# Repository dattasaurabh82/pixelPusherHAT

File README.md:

## PixelPusherHAT
Based on [hzeller's HW hat design](https://github.com/hzeller/rpi-rgb-led-matrix/tree/dfc27c15c224a92496034a39512a274744879e86/adapter/active-3) in the footprint of a HAT, designed in Eagle with minor modifications.

### [The schematic](/assetsREF/PixelPusherV0.pdf)

The managed library for Eagle and Fusion 360 can be found [here](https://library.io/libraries/29033116-PixelPusherV0): 

### _Note_: The GERBERs were generated using [jlcpcb's cam script](https://support.jlcpcb.com/article/137-how-to-generate-gerber-and-drill-files-in-autodesk-eagle).

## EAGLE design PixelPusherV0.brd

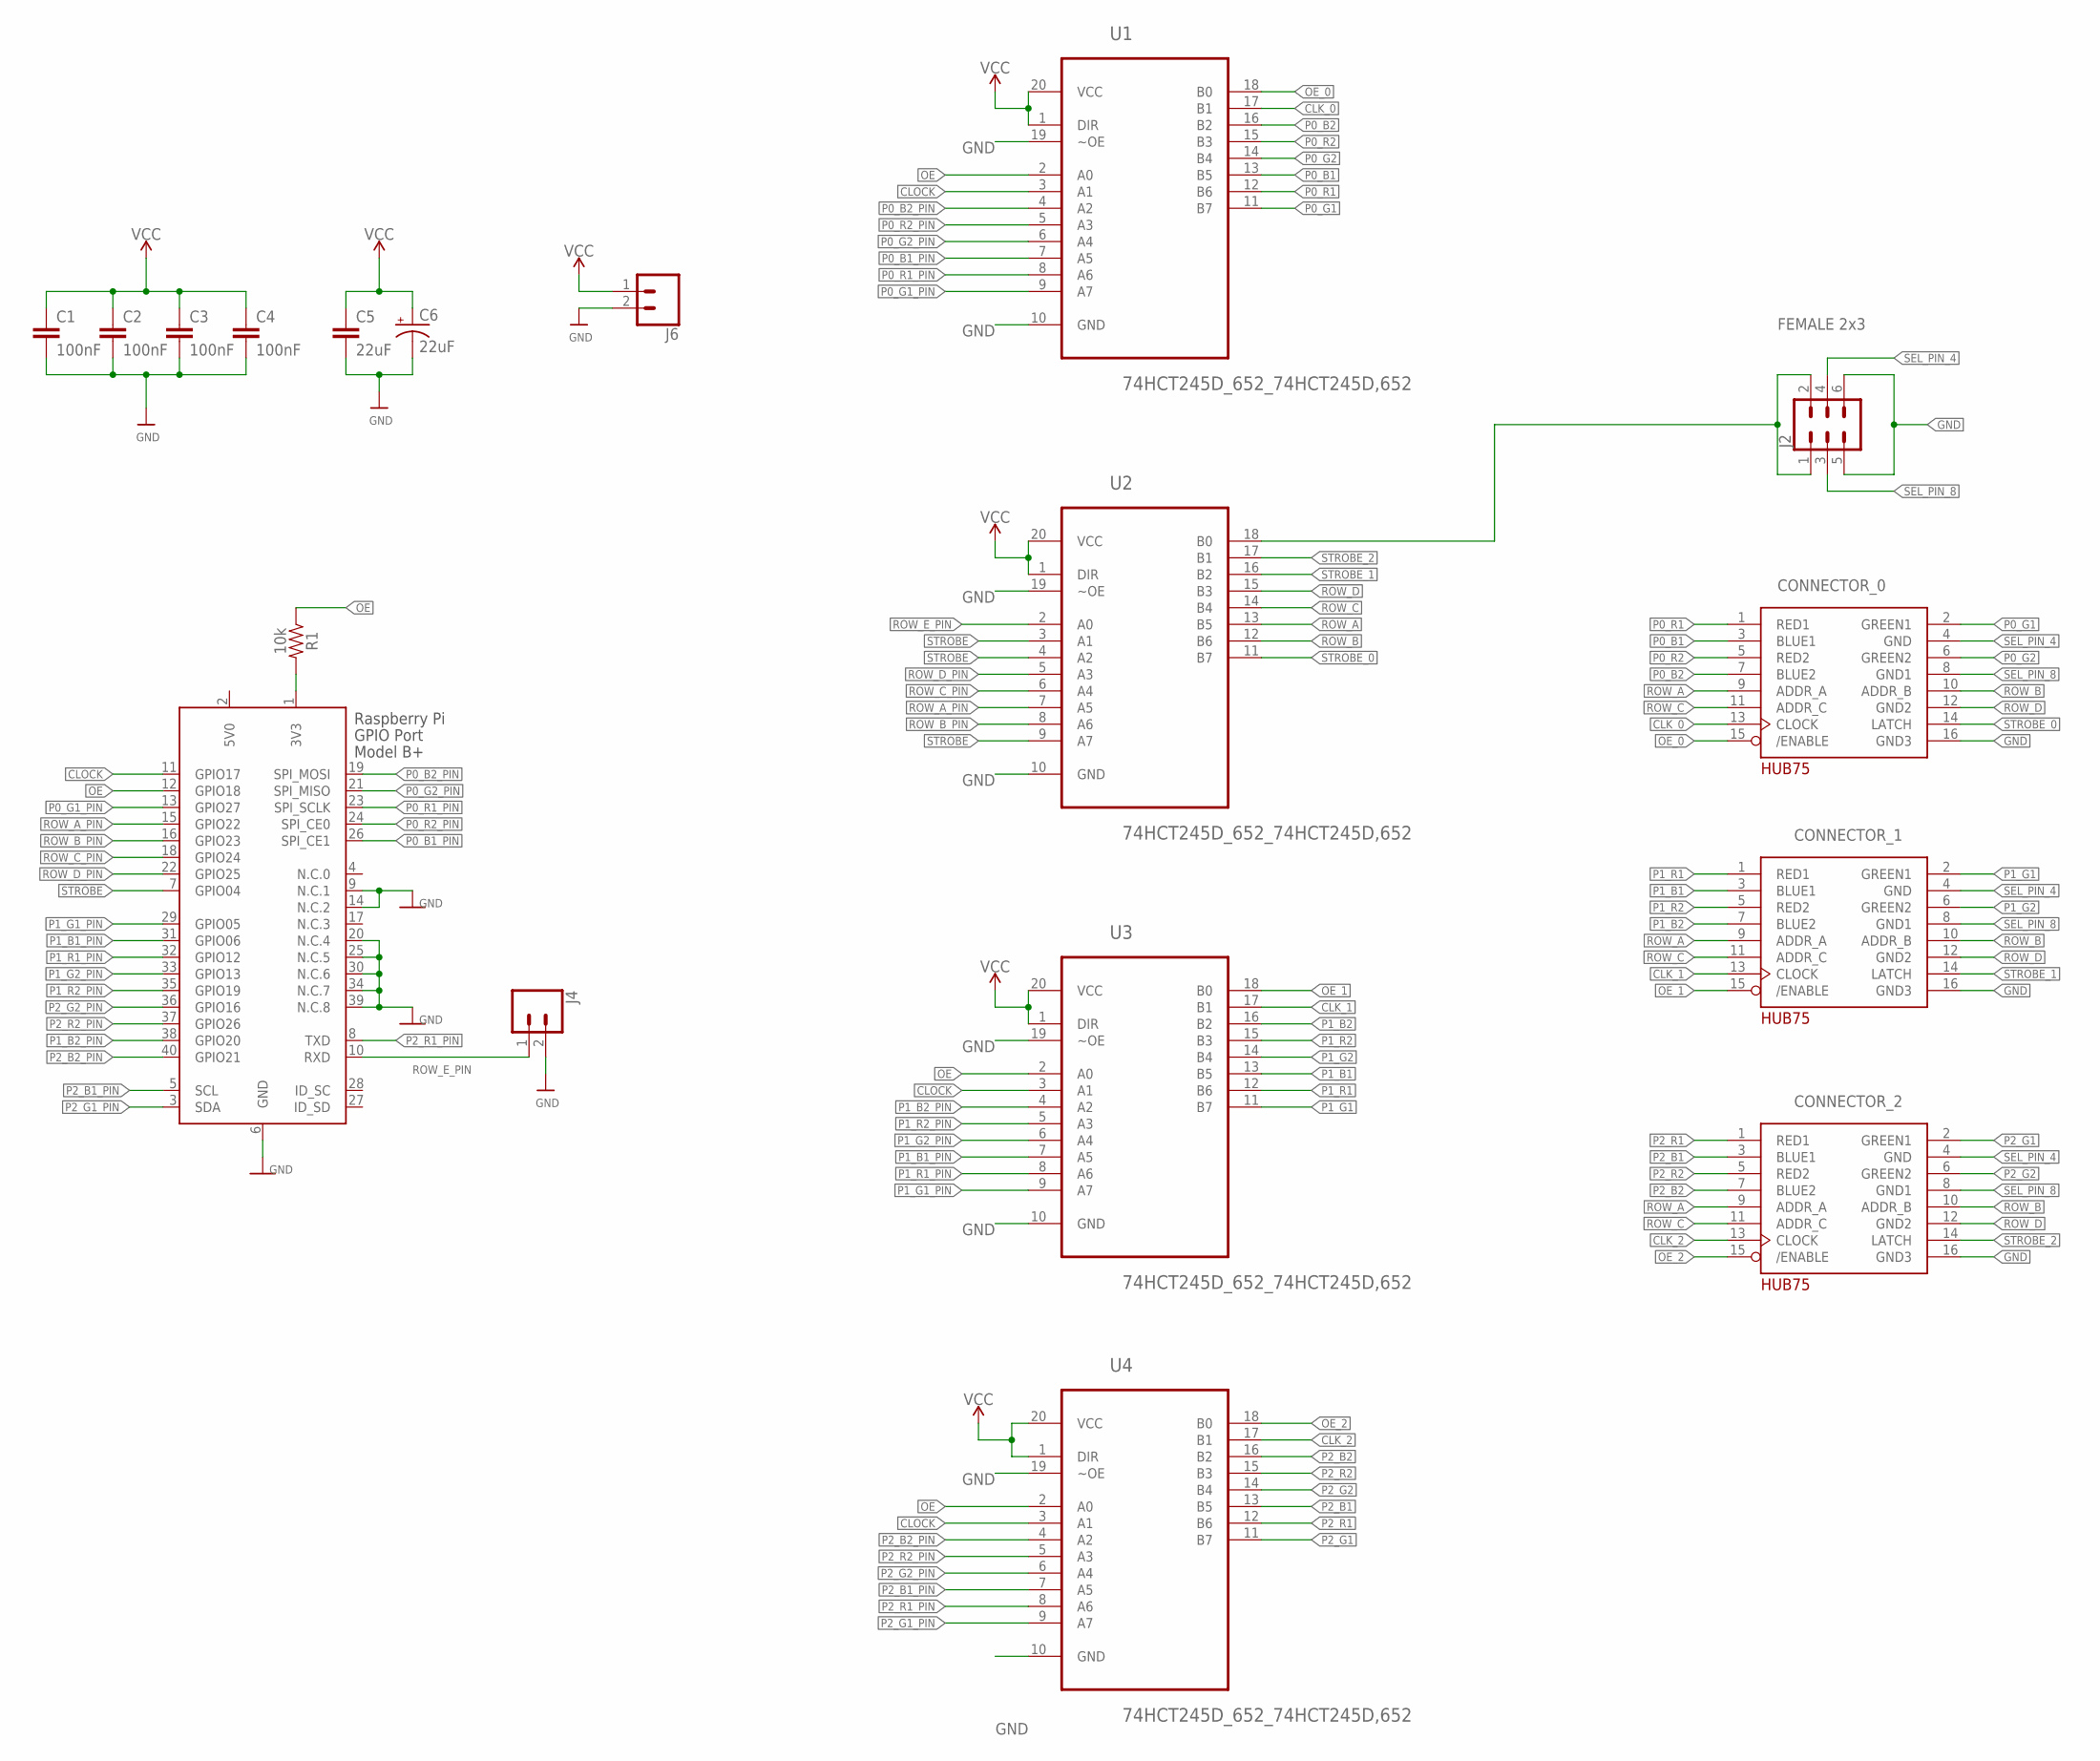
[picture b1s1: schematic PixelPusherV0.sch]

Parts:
C1, C2, C3, C4: 100nF; SPARKFUN-CAPACITORS_0603
C5: 22uF; SPARKFUN-CAPACITORS_0805
C6: 22uF; SPARKFUN-CAPACITORS_PANASONIC_C
CONNECTOR_0, CONNECTOR_1, CONNECTOR_2: ADAFRUIT_HUB75MATRIX; ADAFRUIT_2X08-IDC
J2: FEMALE 2x3; SPARKFUN-CONNECTORS_2X3
J4: SPARKFUN-CONNECTORS_CONN_02; SPARKFUN-CONNECTORS_1X02
J6: SPARKFUN-CONNECTORS_CONN_023.5MM_LOCK; SPARKFUN-CONNECTORS_SCREWTERMINAL-3.5MM-2_LOCK
R1: 10k; SPARKFUN-RESISTORS_0603:1
U1, U2, U3, U4: 74HCT245D_652_74HCT245D,652; 74HCT245D_652_SOIC127P1032X265-20N
X2: RASPBERRYPI_BASTELSTUBE_V13_RASPI_BOARD_B+_HD; RASPBERRYPI_BASTELSTUBE_V13_RASPI_BOARD_B+HAT_DF

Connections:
5V0: X2.2 (5V0)
CLK_0: CONNECTOR_0.13 (CLOCK), U1.17 (B1)
CLK_1: CONNECTOR_1.13 (CLOCK), U3.17 (B1)
CLK_2: CONNECTOR_2.13 (CLOCK), U4.17 (B1)
CLOCK: U1.3 (A1), U3.3 (A1), U4.3 (A1), X2.11 (GPIO17)
GND: C1.2, C2.2, C3.2, C4.2, C5.2, C6.-, CONNECTOR_0.16 (GND3), CONNECTOR_1.16 (GND3), CONNECTOR_2.16 (GND3), J2.5, J2.6, J4.2, J6.2, U1.10 (GND), U1.19 (~OE), U2.10 (GND), U2.19 (~OE), U3.10 (GND), U3.19 (~OE), U4.10 (GND), U4.19 (~OE), X2.6 (GND), X2.9 (N.C.1), X2.14 (N.C.2), X2.20 (N.C.4), X2.25 (N.C.5), X2.30 (N.C.6), X2.34 (N.C.7), X2.39 (N.C.8)
unnamed: J2.1, J2.2, U2.18 (B0)
unnamed: R1.2, X2.1 (3V3)
OE: R1.1, U1.2 (A0), U3.2 (A0), U4.2 (A0), X2.12 (GPIO18)
OE_0: CONNECTOR_0.15 (/ENABLE), U1.18 (B0)
OE_1: CONNECTOR_1.15 (/ENABLE), U3.18 (B0)
OE_2: CONNECTOR_2.15 (/ENABLE), U4.18 (B0)
P0_B1: CONNECTOR_0.3 (BLUE1), U1.13 (B5)
P0_B1_PIN: U1.7 (A5), X2.26 (SPI_CE1)
P0_B2: CONNECTOR_0.7 (BLUE2), U1.16 (B2)
P0_B2_PIN: U1.4 (A2), X2.19 (SPI_MOSI)
P0_G1: CONNECTOR_0.2 (GREEN1), U1.11 (B7)
P0_G1_PIN: U1.9 (A7), X2.13 (GPIO27)
P0_G2: CONNECTOR_0.6 (GREEN2), U1.14 (B4)
P0_G2_PIN: U1.6 (A4), X2.21 (SPI_MISO)
P0_R1: CONNECTOR_0.1 (RED1), U1.12 (B6)
P0_R1_PIN: U1.8 (A6), X2.23 (SPI_SCLK)
P0_R2: CONNECTOR_0.5 (RED2), U1.15 (B3)
P0_R2_PIN: U1.5 (A3), X2.24 (SPI_CE0)
P1_B1: CONNECTOR_1.3 (BLUE1), U3.13 (B5)
P1_B1_PIN: U3.7 (A5), X2.31 (GPIO06)
P1_B2: CONNECTOR_1.7 (BLUE2), U3.16 (B2)
P1_B2_PIN: U3.4 (A2), X2.38 (GPIO20)
P1_G1: CONNECTOR_1.2 (GREEN1), U3.11 (B7)
P1_G1_PIN: U3.9 (A7), X2.29 (GPIO05)
P1_G2: CONNECTOR_1.6 (GREEN2), U3.14 (B4)
P1_G2_PIN: U3.6 (A4), X2.33 (GPIO13)
P1_R1: CONNECTOR_1.1 (RED1), U3.12 (B6)
P1_R1_PIN: U3.8 (A6), X2.32 (GPIO12)
P1_R2: CONNECTOR_1.5 (RED2), U3.15 (B3)
P1_R2_PIN: U3.5 (A3), X2.35 (GPIO19)
P2_B1: CONNECTOR_2.3 (BLUE1), U4.13 (B5)
P2_B1_PIN: U4.7 (A5), X2.5 (SCL)
P2_B2: CONNECTOR_2.7 (BLUE2), U4.16 (B2)
P2_B2_PIN: U4.4 (A2), X2.40 (GPIO21)
P2_G1: CONNECTOR_2.2 (GREEN1), U4.11 (B7)
P2_G1_PIN: U4.9 (A7), X2.3 (SDA)
P2_G2: CONNECTOR_2.6 (GREEN2), U4.14 (B4)
P2_G2_PIN: U4.6 (A4), X2.36 (GPIO16)
P2_R1: CONNECTOR_2.1 (RED1), U4.12 (B6)
P2_R1_PIN: U4.8 (A6), X2.8 (TXD)
P2_R2: CONNECTOR_2.5 (RED2), U4.15 (B3)
P2_R2_PIN: U4.5 (A3), X2.37 (GPIO26)
ROW_A: CONNECTOR_0.9 (ADDR_A), CONNECTOR_1.9 (ADDR_A), CONNECTOR_2.9 (ADDR_A), U2.13 (B5)
ROW_A_PIN: U2.7 (A5), X2.15 (GPIO22)
ROW_B: CONNECTOR_0.10 (ADDR_B), CONNECTOR_1.10 (ADDR_B), CONNECTOR_2.10 (ADDR_B), U2.12 (B6)
ROW_B_PIN: U2.8 (A6), X2.16 (GPIO23)
ROW_C: CONNECTOR_0.11 (ADDR_C), CONNECTOR_1.11 (ADDR_C), CONNECTOR_2.11 (ADDR_C), U2.14 (B4)
ROW_C_PIN: U2.6 (A4), X2.18 (GPIO24)
ROW_D: CONNECTOR_0.12 (GND2), CONNECTOR_1.12 (GND2), CONNECTOR_2.12 (GND2), U2.15 (B3)
ROW_D_PIN: U2.5 (A3), X2.22 (GPIO25)
ROW_E_PIN: J4.1, U2.2 (A0), X2.10 (RXD)
SEL_PIN_4: CONNECTOR_0.4 (GND), CONNECTOR_1.4 (GND), CONNECTOR_2.4 (GND), J2.4
SEL_PIN_8: CONNECTOR_0.8 (GND1), CONNECTOR_1.8 (GND1), CONNECTOR_2.8 (GND1), J2.3
STROBE: U2.3 (A1), U2.4 (A2), U2.9 (A7), X2.7 (GPIO04)
STROBE_0: CONNECTOR_0.14 (LATCH), U2.11 (B7)
STROBE_1: CONNECTOR_1.14 (LATCH), U2.16 (B2)
STROBE_2: CONNECTOR_2.14 (LATCH), U2.17 (B1)
VCC: C1.1, C2.1, C3.1, C4.1, C5.1, C6.+, J6.1, U1.1 (DIR), U1.20 (VCC), U2.1 (DIR), U2.20 (VCC), U3.1 (DIR), U3.20 (VCC), U4.1 (DIR), U4.20 (VCC)

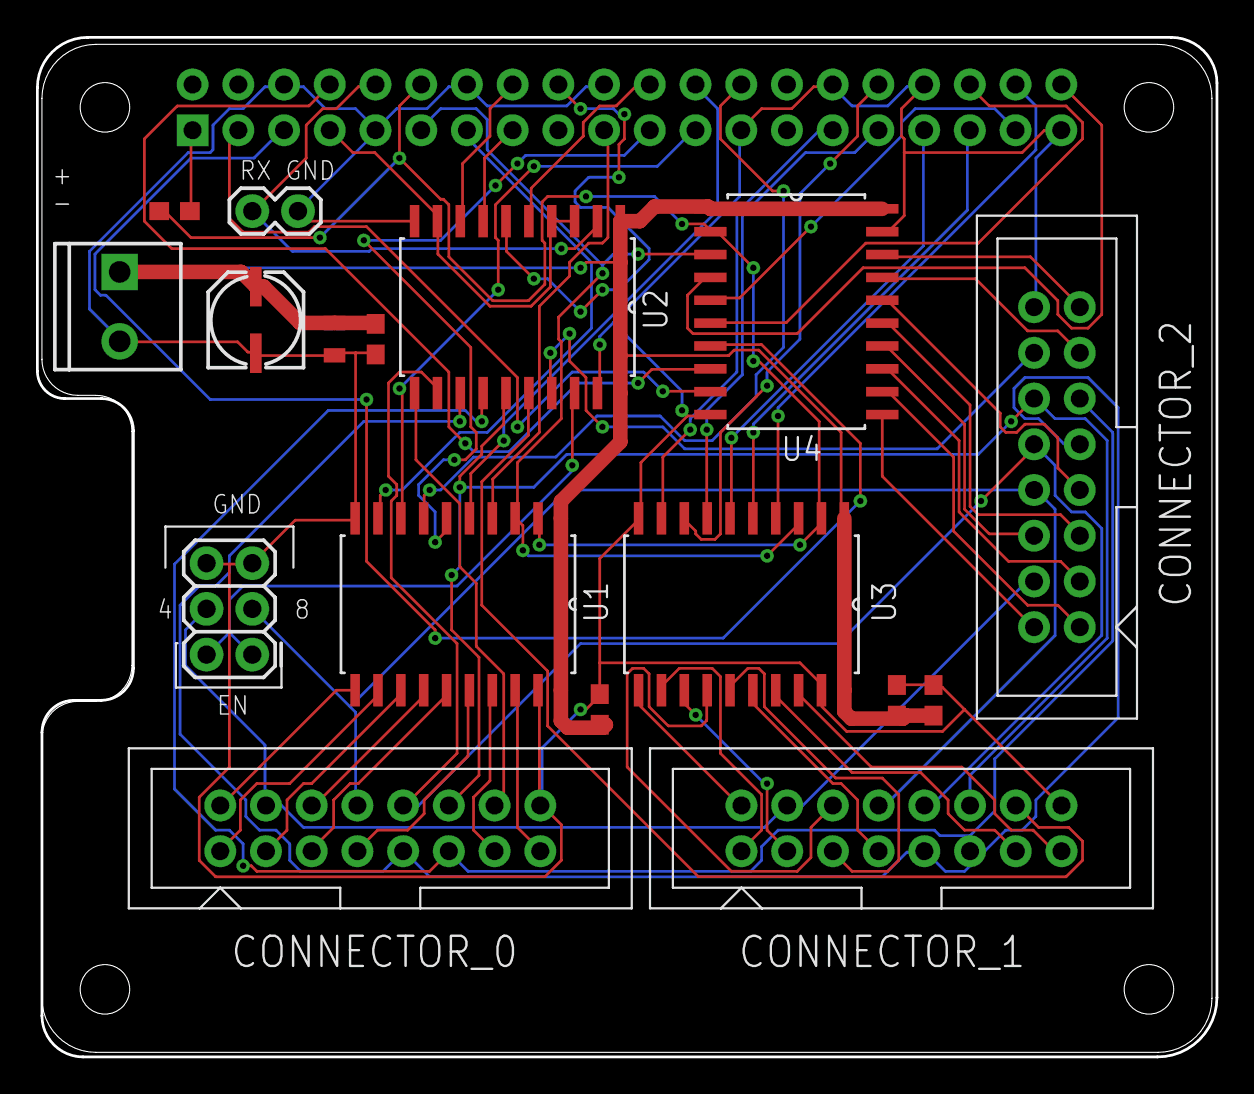
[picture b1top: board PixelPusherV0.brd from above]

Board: 2 copper layers, 65.5 x 56.6 mm, 18 parts (0 on the bottom side), 63 nets.

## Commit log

2021-05-31 updated heading
2021-05-31 added license
2021-05-31 added topimage
2021-05-31 added bottom image
2021-05-31 resized bottom image

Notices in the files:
parts and their libraries:
microbuilder: This work is placed in the public domain, and may be freely used for commercial and non-commercial work with the following conditions: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
